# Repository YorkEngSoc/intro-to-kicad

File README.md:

# Intro to KiCad

## Overview

Welcome to the **Intro to KiCad** repository. This lab script is designed to introduce the fundamentals of PCB design using KiCad, a powerful and free software suite for electronic design automation (EDA). Throughout this lab, you'll go through the process of creating a **stylophone**, a simple electronic musical instrument, while learning the key steps in PCB design, including schematic creation, footprint assignment, PCB layout, and exporting Gerber files for manufacturing.

This repository contains all necessary libraries, project files, and references to help you complete the lab.

## Repository Structure

```bash
intro-to-kicad/
│
├── BOM/                 # Bill of Materials for the Stylophone project
├── Example Project/     # Completed project files for reference
├── Libraries/           # Symbol and footprint libraries
├── Pictures/            # Images for documentation
```

Please read the PDF lab script in the root of the repo

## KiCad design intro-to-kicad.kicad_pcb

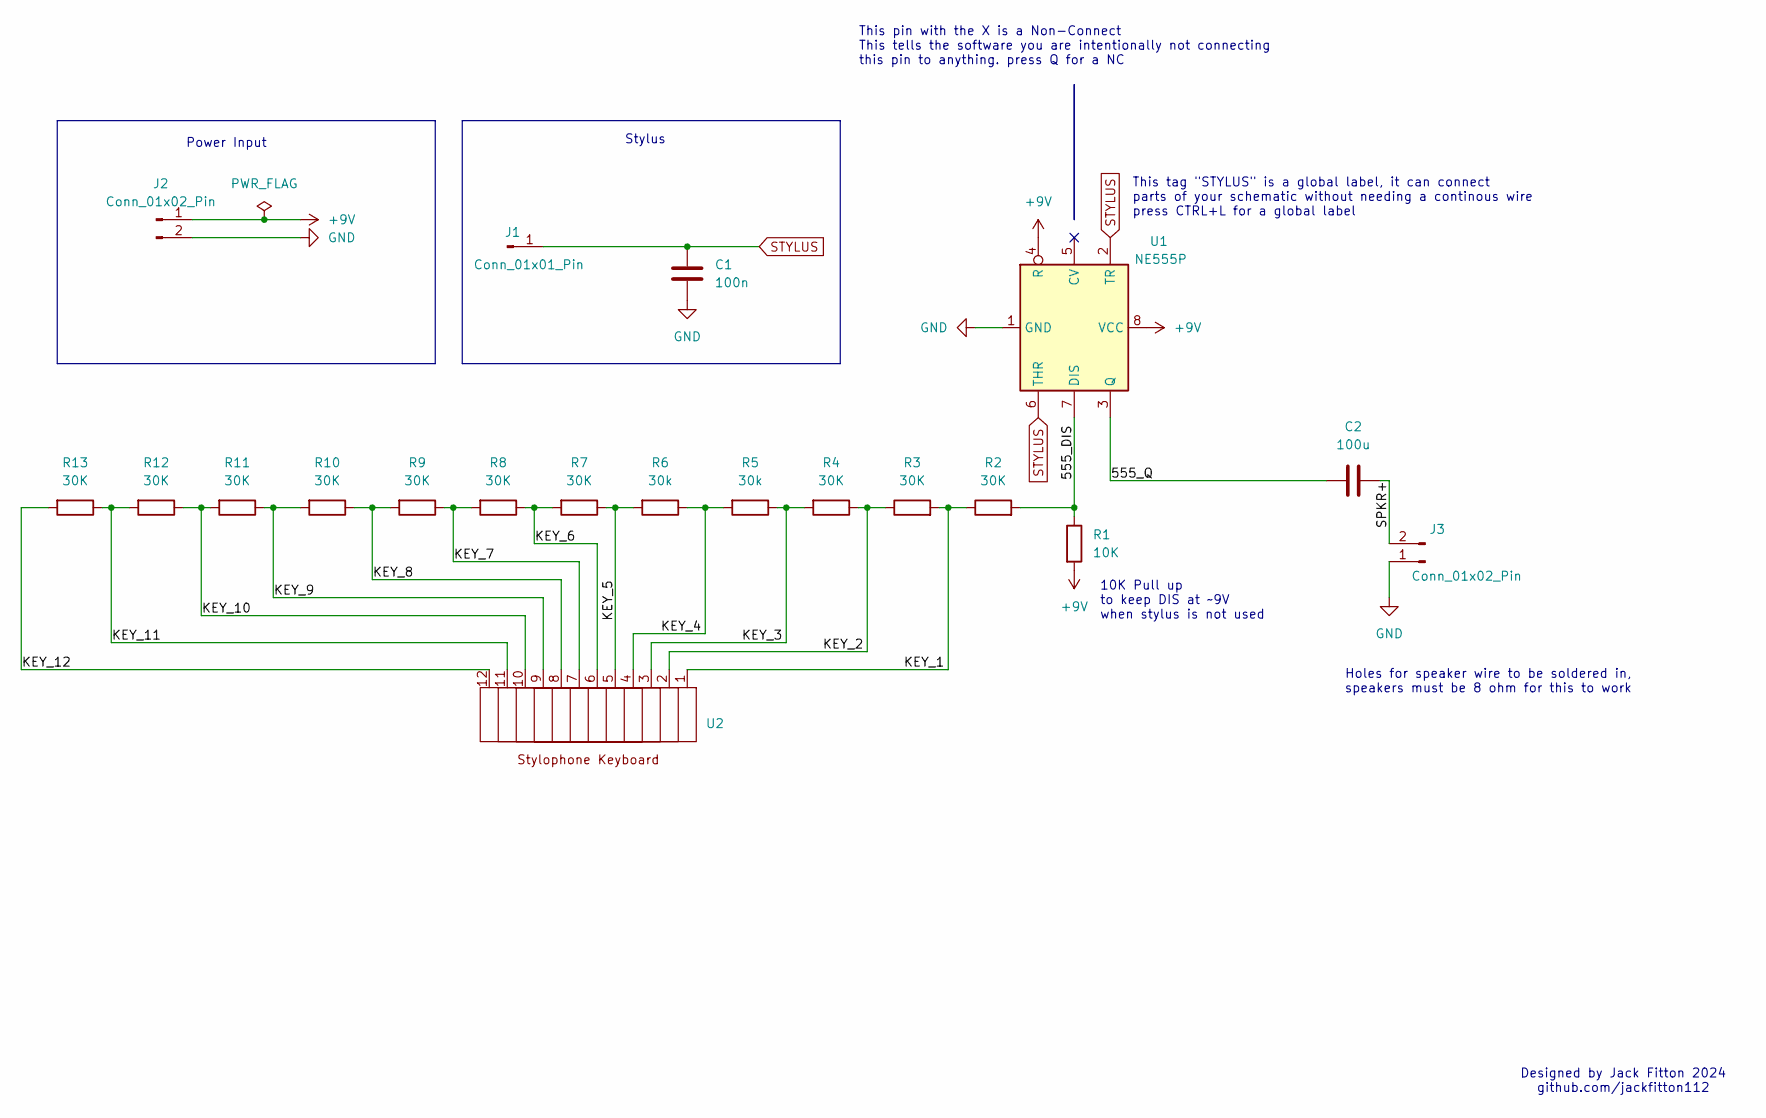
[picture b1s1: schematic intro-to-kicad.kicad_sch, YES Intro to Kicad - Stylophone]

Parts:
C1: 100n; C_Axial_L5.1mm_D3.1mm_P10.00mm_Horizontal
C2: 100u; CP_Radial_D7.5mm_P2.50mm
J1: Conn_01x01_Pin; PinHeader_1x01_P2.54mm_Vertical
J2, J3: Conn_01x02_Pin; PinHeader_1x02_P2.54mm_Vertical
R1: 10K; R_Axial_DIN0204_L3.6mm_D1.6mm_P5.08mm_Horizontal
R2, R3, R4, R7, R8, R9, R10, R11, R12, R13: 30K; R_Axial_DIN0204_L3.6mm_D1.6mm_P5.08mm_Horizontal
R5, R6: 30k; R_Axial_DIN0204_L3.6mm_D1.6mm_P5.08mm_Horizontal
U1: NE555P; DIP-8_W7.62mm
U2: 12 Key Keyboard Fancy

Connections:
+9V: J2.1, R1.2, U1.4 (R), U1.8 (VCC)
/555_DIS: R1.1, R2.2, U1.7 (DIS)
/555_Q: C2.1, U1.3 (Q)
/KEY_1: R2.1, R3.2, U2.1
/KEY_2: R3.1, R4.1, U2.2
/KEY_3: R4.2, R5.1, U2.3
/KEY_4: R5.2, R6.1, U2.4
/KEY_5: R6.2, R7.1, U2.5
/KEY_6: R7.2, R8.1, U2.6
/KEY_7: R8.2, R9.1, U2.7
/KEY_8: R9.2, R10.1, U2.8
/KEY_9: R10.2, R11.1, U2.9
/KEY_10: R11.2, R12.1, U2.10
/KEY_11: R12.2, R13.1, U2.11
/KEY_12: R13.2, U2.12
/SPKR+: C2.2, J3.2
GND: C1.2, J2.2, J3.1, U1.1 (GND)
STYLUS: C1.1, J1.1, U1.2 (TR), U1.6 (THR)

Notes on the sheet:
Stylus
This tag "STYLUS" is a global label, it can connect parts of your schematic without needing a continous wire press CTRL+L for a global label
Holes for speaker wire to be soldered in, speakers must be 8 ohm for this to work
Power Input
10K Pull up to keep DIS at ~9V when stylus is not used
This pin with the X is a Non-Connect This tells the software you are intentionally not connecting this pin to anything. press Q for a NC
Designed by Jack Fitton 2024 github.com/jackfitton112

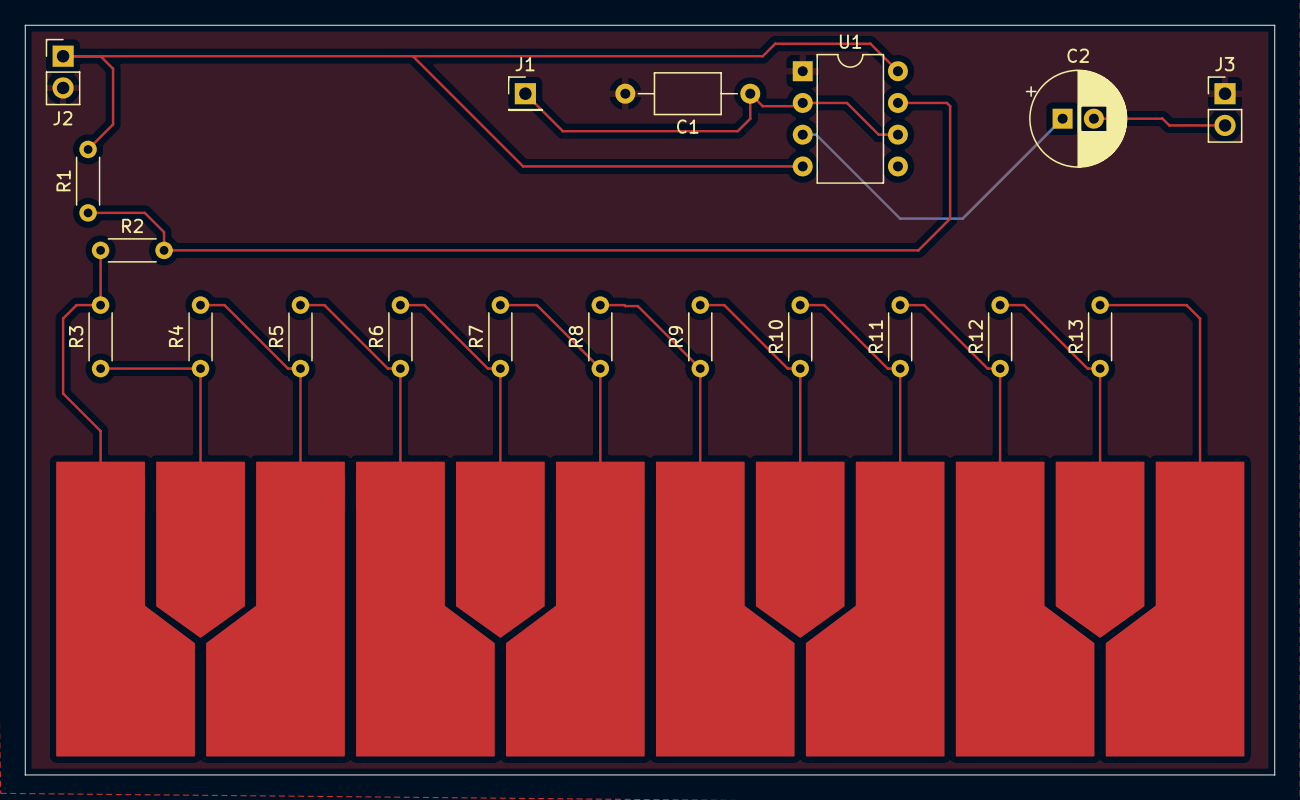
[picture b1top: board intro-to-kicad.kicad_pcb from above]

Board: 2 copper layers, 100.0 x 60.0 mm, 20 parts (0 on the bottom side), 18 nets.

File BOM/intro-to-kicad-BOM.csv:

"Id";"Designator";"Footprint";"Quantity";"Designation";"Supplier and ref";
1;"R6,R5";"R_Axial_DIN0204_L3.6mm_D1.6mm_P5.08mm_Horizontal";2;"30k";;;
2;"J3,J2";"PinHeader_1x02_P2.54mm_Vertical";2;"Conn_01x02_Pin";;;
3;"R10,R3,R8,R2,R12,R13,R11,R9,R7,R4";"R_Axial_DIN0204_L3.6mm_D1.6mm_P5.08mm_Horizontal";10;"30K";;;
4;"C2";"CP_Radial_D7.5mm_P2.50mm";1;"100u";;;
5;"J1";"PinHeader_1x01_P2.54mm_Vertical";1;"Conn_01x01_Pin";;;
6;"U1";"DIP-8_W7.62mm";1;"NE555P";;;
7;"C1";"C_Axial_L5.1mm_D3.1mm_P10.00mm_Horizontal";1;"100n";;;
8;"R1";"R_Axial_DIN0204_L3.6mm_D1.6mm_P5.08mm_Horizontal";1;"10K";;;
9;"U2";"12 Key Keyboard Fancy";1;"~";;;

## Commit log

2024-10-02 updated docs
2024-10-12 finalised project
2024-10-12 restructured project
2024-10-12 removed old files
2024-10-15 updated lab script to clarify some bits
    after testing the script we found it was difficult to import parts based off the description given in the lab script and it was unclear how to swap to the PCB editor
2024-10-16 updated image names and added blank example project with sym and fp already included
2024-10-16 updated image link
2024-10-16 fixed lab script
    added clarification about symbols and fixed BOM
2024-10-16 fixed lab script
